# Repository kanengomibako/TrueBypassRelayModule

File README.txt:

True Bypass Relay Module

ブログ記事→https://drugscore.blog.fc2.com/blog-entry-244.html

秋月電子にある特価ラッチリレーEA2-5TNAGを利用したトゥルーバイパスモジュールです。ロジックICを利用しているのでプログラミングが不要です。TC4069UBP、TC74HCU04APで動作確認しています。在庫限りの部品が多いのでご注意ください。

参考サイト→Using a latching relay driver for true bypass(http://www.fredric.co.uk/blog/134-Using-a-latching-relay-driver-for-true-bypass)

当初ラッチリレーのピン配置の表裏が逆というミスがあったので、公開しているデータはエラー修正済のRev.B基板です。エラー修正前のRev.A基板をお持ちの方は必ず修正方法をご確認下さい。

＜接続方法＞
SW1→モーメンタリスイッチをつなぎます。接続は左右入れ替わってもOKです。
LED→エフェクトオン時に点灯するLEDをつなぎます。四角いパッドになっている方がカソード側です。
GND→GNDをつなぎます。
IN→入力ジャックをつなぎます。
OUT→出力ジャックをつなぎます。
SND→エフェクター基板の入力へつなぎます。
RTN→エフェクター基板からの出力をつなぎます。
VCC→+9V電源をつなぎます。

＜エラーありRev.A基板の修正方法＞
ラッチリレーをそのままの向き（棒状の印が付いている方が下側）で裏側に取り付けます。スペースの都合で裏側に取り付けられない場合は、LEDの配線を変えます。+5VがきているところにLEDのアノードをつなぎ、LEDのアノードを接続するはずだったところにLEDのカソードをつなぎます。

＜パーツリスト＞
7	100n	C1, C2, C3, C4, C5, C6, C7 ※積層セラミックコンデンサ
1	10u	C8　※電解コンデンサ

1	1k	R3
2	10k	R6, R7
3	100k	R1, R4, R5
1	1M	R2

3	1N4148	D1, D2, D3
1	LED	D4

2	2SC1815-GR	Q1, Q2
1	EA2-5TNAG	U1
1	TC4069UBP	U2
1	78L05	U3

1	FS	SW1　※SPSTモーメンタリスイッチ

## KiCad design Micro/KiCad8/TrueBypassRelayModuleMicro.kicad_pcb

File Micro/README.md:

# True Bypass Relay Module Micro

<br>

モーメンタリースイッチを接続して、エフェクターのトゥルーバイパスとインジケーターLED切替を行うことができるモジュールです。

### 配線方法

<br>

- IN → 入力ジャック
- SND → エフェクト基板の入力
- GND → グラウンド（アース）
- RTN → エフェクト基板の出力
- OUT → 出力ジャック
- 9V → 電源
- LED → LEDの電流制限抵抗とLED<br>※ エフェクトオン時に5Vが出力されます。電流制限抵抗の抵抗値は470Ω以上を推奨します。
- SW → スイッチ（接続は上下入れ替わってもOK）<br>※ モーメンタリー（モメンタリ）のスイッチを使用します。SPST（単極単投、1回路1接点）のものが入手しやすいです。

### 機能設定
スイッチを押す度にエフェクトオンとバイパスが切り替わる通常モードと、スイッチを押している間のみエフェクトオンになるモーメンタリーモードがあります。また、電源を入れたときに自動でエフェクトオンにするかどうかを設定できます。設定は自動保存され、電源を切っても記憶されています。

- 起動時エフェクトオン機能切替<br>スイッチを押しながら電源を入れます。設定完了時にLEDが2回点滅します。
- モーメンタリーモード・通常モード切替<br> スイッチを押しながら電源を入れ、そのまま約3秒間スイッチを押し続けます。設定完了時にLEDが3回点滅します。<br>※ モーメンタリーモードの状態で起動時エフェクトオンに設定にすると、スイッチを押している間のみバイパス状態となるモードになります。

### 資料
- [True Bypass Relay Module Micro 製作に関する記事](https://kanengomibako.github.io/pages/00349.html)

| 主な仕様 |  |
| - | - |
| 出荷時設定 | 通常モード　起動時エフェクトバイパス |
| 使用可能電源電圧範囲 | 7V ～ 20V |
| 消費電流 | 3mA（オン・オフ切替の一瞬のみ21mA消費電流増加） |
| 外形寸法 | 幅 18 mm × 奥行 15 mm × 高さ 7 mm |
| 質量 | 約 1.5 g |

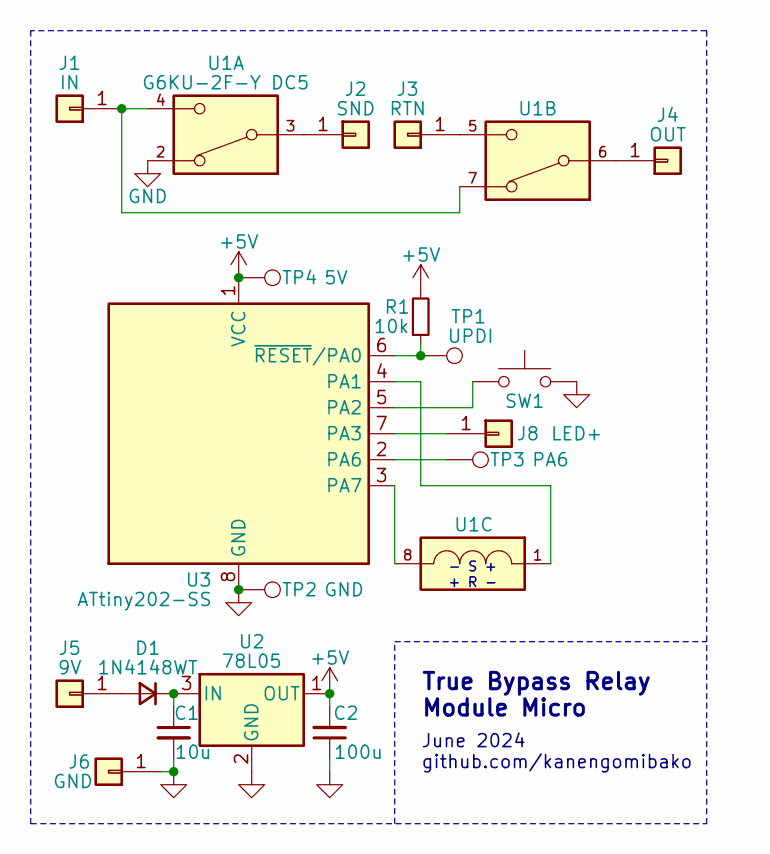
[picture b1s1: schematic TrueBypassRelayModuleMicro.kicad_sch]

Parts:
C1: 10u; C_0603_1608Metric
C2: 100u; C_1206_3216Metric
D1: 1N4148WT; D_SOD-523_HandSoldering
J1: IN; my_WirePad_1mmDrill
J2: SND; my_WirePad_1mmDrill
J3: RTN; my_WirePad_1mmDrill
J4: OUT; my_WirePad_1mmDrill
J5: 9V; my_WirePad_1mmDrill
J6: GND; my_WirePad_1mmDrill
J8: LED+; my_WirePad_1mmDrill
R1: 10k; R_0603_1608Metric
SW1: SW1; PinHeader_1x02_P2.54mm_Vertical
TP1: UPDI; my_TestPoint_2mm
TP2: GND; my_TestPoint_2mm
TP3: PA6; my_TestPoint_2mm
TP4: 5V; my_TestPoint_2mm
U1: G6KU-2F-Y DC5; Relay_DPDT_Omron_G6K-2F-Y
U2: 78L05; SOT-89-3
U3: ATtiny202-SS; SOIC-8_3.9x4.9mm_P1.27mm

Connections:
+5V: C2.2, R1.2, TP4.1, U2.1 (OUT), U3.1 (VCC)
GND: C1.2, C2.1, J6.1, SW1.2, TP2.1, U1.2, U2.2 (GND), U3.8 (GND)
unnamed: D1.2 (A), J5.1
unnamed: C1.1, D1.1 (K), U2.3 (IN)
unnamed: J1.1, U1.4, U1.7
unnamed: J2.1, U1.3
unnamed: J3.1, U1.5
unnamed: J4.1, U1.6
unnamed: J8.1, U3.7 (PA3)
unnamed: U1.1, U3.4 (PA1)
unnamed: SW1.1, U3.5 (PA2)
unnamed: TP3.1, U3.2 (PA6)
unnamed: U1.8, U3.3 (PA7)
unnamed: R1.1, TP1.1, U3.6 (~RESET/PA0)

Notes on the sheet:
True Bypass Relay Module Micro
June 2024 github.com/kanengomibako
- S + + R -

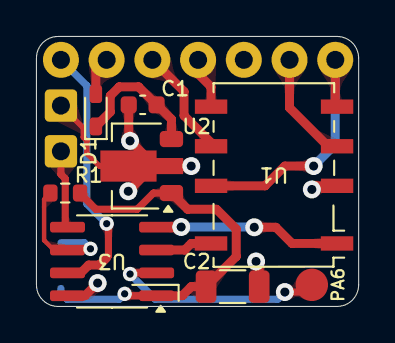
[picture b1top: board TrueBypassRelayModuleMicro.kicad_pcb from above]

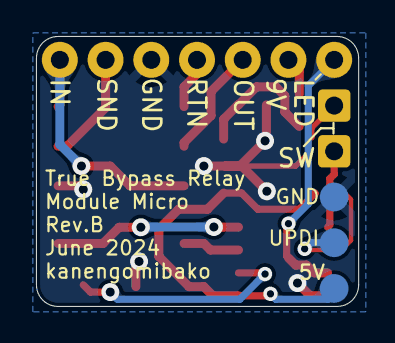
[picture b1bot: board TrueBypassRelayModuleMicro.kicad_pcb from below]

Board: 2 copper layers, 17.9 x 15.0 mm, 19 parts (11 on the bottom side), 14 nets.

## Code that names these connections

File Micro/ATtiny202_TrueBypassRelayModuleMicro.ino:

/*
True Bypass Relay Module Micro
v1.0 20240709
https://github.com/kanengomibako

ヒューズビット設定
BOD Mode when Active/Sleeping: Enabled/Enabled
BOD Voltage Level: 3.7V (Unofficial)
Chip: ATtiny202
Clock: 1 MHz internal
Save EEPROM: EEPROM retained
*/

#include <EEPROM.h>

#define SHORT_PUSH_MSEC 10                         // スイッチ短押し時間 ミリ秒
#define RELAY_DRIVE_MSEC 11                        // リレーコイル駆動時間 ミリ秒 16まで
const long shortPushCount = 10 * SHORT_PUSH_MSEC;  // 10カウントで1ms

bool fxState = true;    // エフェクトオンオフ状態 true: オン
long swOnCnt = 0;       // スイッチを押している間カウントアップ
long swOffCnt = 0;      // スイッチを押していない間カウントアップ
int onStart = 1;        // 起動時エフェクトオン設定
int momentaryMode = 0;  // モーメンタリモード設定
const int addr0 = 0;    // EEPROM 起動時オンオフ設定書き込み先アドレス
const int addr1 = 1;    // EEPROM モーメンタリモード設定書き込み先アドレス

// エフェクトオン動作
void fxOn() {
  digitalWrite(PIN_PA7, LOW);
  digitalWrite(PIN_PA1, HIGH);
  delayMicroseconds(1000 * RELAY_DRIVE_MSEC);
  digitalWrite(PIN_PA1, LOW);
  digitalWrite(PIN_PA3, HIGH);  // LED
  fxState = true;
}

// エフェクトオフ動作
void fxOff() {
  digitalWrite(PIN_PA1, LOW);
  digitalWrite(PIN_PA7, HIGH);
  delayMicroseconds(1000 * RELAY_DRIVE_MSEC);
  digitalWrite(PIN_PA7, LOW);
  digitalWrite(PIN_PA3, LOW);  // LED
  fxState = false;
}

// LED点滅
void blink(int n) {
  for (int i = 0; i < n; i++) {
    digitalWrite(PIN_PA3, HIGH);
    delay(50);
    digitalWrite(PIN_PA3, LOW);
    delay(150);
  }
}

// 電源電圧低下時割り込み
ISR(BOD_VLM_vect) {
  PORTA.OUTCLR = PIN3_bm;       // 高速 PA3 LOW (LED)
  PORTA.OUTSET = PIN7_bm;       // 高速 PA7 HIGH
  fxOff();                      // エフェクトオフ発動
  BOD.INTFLAGS = BOD_VLMIF_bm;  // 割り込みフラグクリア
}

void setup() {
  delay(100);  // 電源立ち上がり待機

  // ピン設定
  pinMode(PIN_PA1, OUTPUT);        // PA1: リレーセット エフェクトオン
  pinMode(PIN_PA2, INPUT_PULLUP);  // PA2: スイッチ読み取り 内部プルアップ
  pinMode(PIN_PA3, OUTPUT);        // PA3: LED出力
  pinMode(PIN_PA6, OUTPUT);        // PA6: 不使用
  pinMode(PIN_PA7, OUTPUT);        // PA7: リレーリセット エフェクトバイパス
  digitalWrite(PIN_PA1, LOW);
  digitalWrite(PIN_PA3, LOW);
  digitalWrite(PIN_PA6, LOW);
  digitalWrite(PIN_PA7, LOW);

  // 設定読み込み
  onStart = EEPROM.read(addr0);
  momentaryMode = EEPROM.read(addr1);

  // スイッチを押しながら起動
  while (digitalRead(PIN_PA2) == LOW) {
    swOnCnt++;
    delay(1);
    if (swOnCnt == 20) {  // 短押し時 起動時オンオフ設定変更
      onStart = !onStart;
      EEPROM.write(addr0, onStart);
      blink(2);
    }
    if (swOnCnt == 3000) {  // 長押し時 モーメンタリモード設定変更
      momentaryMode = !momentaryMode;
      onStart = 0;  // 起動時オフ設定にする（スイッチを押している間だけエフェクトオン）
      EEPROM.write(addr0, onStart);
      EEPROM.write(addr1, momentaryMode);
      blink(3);
    }
  }
  swOnCnt = 0;

  // 起動時オンオフ実行
  if (onStart) fxOn();
  else fxOff();

  // 電源電圧低下時割り込み設定
  BOD.VLMCTRLA = BOD_VLMLVL_25ABOVE_gc;              // VLM閾値 3.7V * 1.25 = 4.6V
  BOD.INTCTRL = BOD_VLMIE_bm | BOD_VLMCFG_BELOW_gc;  // VLM割り込み有効 閾値を下回った時発動
}

void loop() {
  if (digitalRead(PIN_PA2) == LOW) {
    swOnCnt++;  // スイッチを押した時カウントアップ
    swOffCnt = 0;
  } else {
    swOffCnt++;  // スイッチを離した時カウントアップ
    swOnCnt = 0;
  }

  if (momentaryMode) {  // モーメンタリーモード
    if (onStart) {      // 起動時エフェクトオン → フットスイッチ押下時にエフェクトオフ
      if (swOnCnt == shortPushCount) fxOff();
      if (swOffCnt == shortPushCount) fxOn();
    } else {  // 起動時エフェクトオフ → フットスイッチ押下時にエフェクトオン
      if (swOnCnt == shortPushCount) fxOn();
      if (swOffCnt == shortPushCount) fxOff();
    }
  } else {  // オルタネートモード
    if (swOnCnt == shortPushCount) {
      fxState = !fxState;
      if (fxState) fxOn();
      else fxOff();
    }
  }

  delayMicroseconds(20);  // ループ一回が0.1msになるよう調整
  //PORTA.OUTTGL = PIN3_bm;  // 高速LEDトグル ループ時間確認用
}

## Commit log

2019-06-12 Create KiCad data
2024-07-08 Reorganized folders
2024-07-11 Add True Bypass Relay Module Micro
2025-05-16 Fix links
